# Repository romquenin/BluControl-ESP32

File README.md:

# BluControl-ESP32: Dreamcast & GameCube

Wireless mods for original retro controllers, built on [BluControl-ESP32](https://github.com/JPZV/BluControl-ESP32) by JPZV.

An ESP32 is placed inside the controller and reads it the way the console would. The controller's own board is kept intact. The ESP32 then talks Bluetooth, either as a **Nintendo Switch Pro Controller** or as a generic gamepad for **[BlueRetro](https://github.com/darthcloud/BlueRetro)** adapters.

This fork only keeps what these controllers need. For the other controllers supported by BluControl (N64, SNES, NES, PSX…), use the [original project](https://github.com/JPZV/BluControl-ESP32).

## Controllers

| Controller | Status | Page |
|---|---|---|
| **Sega Dreamcast** | ✅ v1: buttons, stick, analog triggers, and the **VMU** (saves and screen) through a modified BlueRetro, with 4 VMU pages (800 blocks) | [docs/dreamcast.md](docs/dreamcast.md) |
| **Nintendo GameCube** | ✅ v1: in Yakara's style, with rumble through the BluPower GC board · 🚧 v2 "cable mode", with the controller board kept intact | [docs/gamecube.md](docs/gamecube.md) |

Ready-to-flash firmware is in the [Releases](https://github.com/romquenin/BluControl-ESP32/releases). Each release contains the latest firmware for every controller.

## The BluPower GC board

A small board (20.3 × 15.2 mm) made for this project:
- an AP2112K low-dropout 3.3 V regulator for the ESP32, which keeps working as the LiPo battery runs down, where the usual AMS1117 cannot;
- a MOSFET that drives the GameCube rumble motor.

It is fully populated for the GameCube version 1. The Dreamcast and the GameCube cable mode only use its regulator. KiCad project, Gerbers and JLCPCB files are in [`hardware/blupower_gc/`](hardware/blupower_gc). Parts, wiring and ordering: [docs/blupower.md](docs/blupower.md).

## Repository layout

| Path | Content |
|---|---|
| `blu-common/` | Shared components. Dreamcast Maple bus driver: `dc_maple.c` |
| `blu-switch/` | Switch Pro Controller mode |
| `blu-generic/` | BLE gamepad mode for BlueRetro, including the VMU service |
| `blu-ota/` | Wi-Fi update mode |
| `configs/` | Build configuration per controller |
| `patches/` | Small changes to JPZV's submodules, applied by `build.sh` |
| `blueretro/` | Patch for BlueRetro v25.04 (Dreamcast VMU support) |
| `hardware/` | BluPower GC board (KiCad, Gerbers, JLCPCB files) |
| `docs/` | Documentation |

## Building

Requires **ESP-IDF v5.0** and Node.js (for the update web page).

```sh
git clone --recursive https://github.com/romquenin/BluControl-ESP32
cd BluControl-ESP32
. $IDF_PATH/export.sh
./build.sh dreamcast    # or: ./build.sh gamecube
```

The script applies the patches, builds the three modes, and writes two files to `release/`:
- `BluControl_<config>_FULL_0x0.bin`: full USB flash at address 0x0;
- `BluControl_<config>.updpkg`: Wi-Fi update.

The modified BlueRetro is built separately: see [blueretro/README.md](blueretro/README.md).

## Credits

- **[JPZV](https://github.com/JPZV)**, author of [BluControl-ESP32](https://github.com/JPZV/BluControl-ESP32), which this project is built on, and of the forks it uses: [BluControl-SDK-ESP32](https://github.com/JPZV/BluControl-SDK-ESP32), [HOJA-LIB-ESP32](https://github.com/JPZV/HOJA-LIB-ESP32), [ESP32-BLE-Gamepad-idf](https://github.com/JPZV/ESP32-BLE-Gamepad-idf), [esp-nimble-cpp](https://github.com/JPZV/esp-nimble-cpp).
- The original authors of those libraries:
  - **HandHeldLegend**: HOJA-LIB-ESP32, the Switch Pro Controller emulation;
  - **[lemmingDev](https://github.com/lemmingDev)**: ESP32-BLE-Gamepad;
  - **[h2zero](https://github.com/h2zero)**: esp-nimble-cpp.
- **[darthcloud](https://github.com/darthcloud)**: [BlueRetro](https://github.com/darthcloud/BlueRetro). The Dreamcast VMU support is a patch on BlueRetro v25.04.
- **[dpedu.io](https://dpedu.io/article/2015-03-11/nintendo-64-joystick-pinout-arduino)**: credited by the original BluControl for his article on N64 analogs.
- **[Yakara](https://github.com/yakaracolombia)**: for the [GameCube wireless tutorial](https://github.com/yakaracolombia/esp32-online-tool/blob/main/gamecube.md) that inspired our GameCube work.

## License

Same license as BluControl-ESP32: [CC BY-NC-SA 4.0](LICENSE). Non-commercial use only, with attribution, and derivatives must be shared under the same license. Submodules and the BlueRetro patch keep their own licenses: GPL-3.0 for BluControl-SDK, CC BY-NC-SA 4.0 for HOJA-LIB, MIT for ESP32-BLE-Gamepad, Apache-2.0 for esp-nimble-cpp and BlueRetro.

Maintained by [romquenin](https://github.com/romquenin).

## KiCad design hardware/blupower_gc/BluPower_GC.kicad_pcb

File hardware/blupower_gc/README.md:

# BluPower GC: design files

KiCad project, schematic (PDF), JLCPCB fabrication files (`fab/`) and generation scripts (`tools/`).

Documentation, parts list, pinout and wiring: [docs/blupower.md](../../docs/blupower.md).

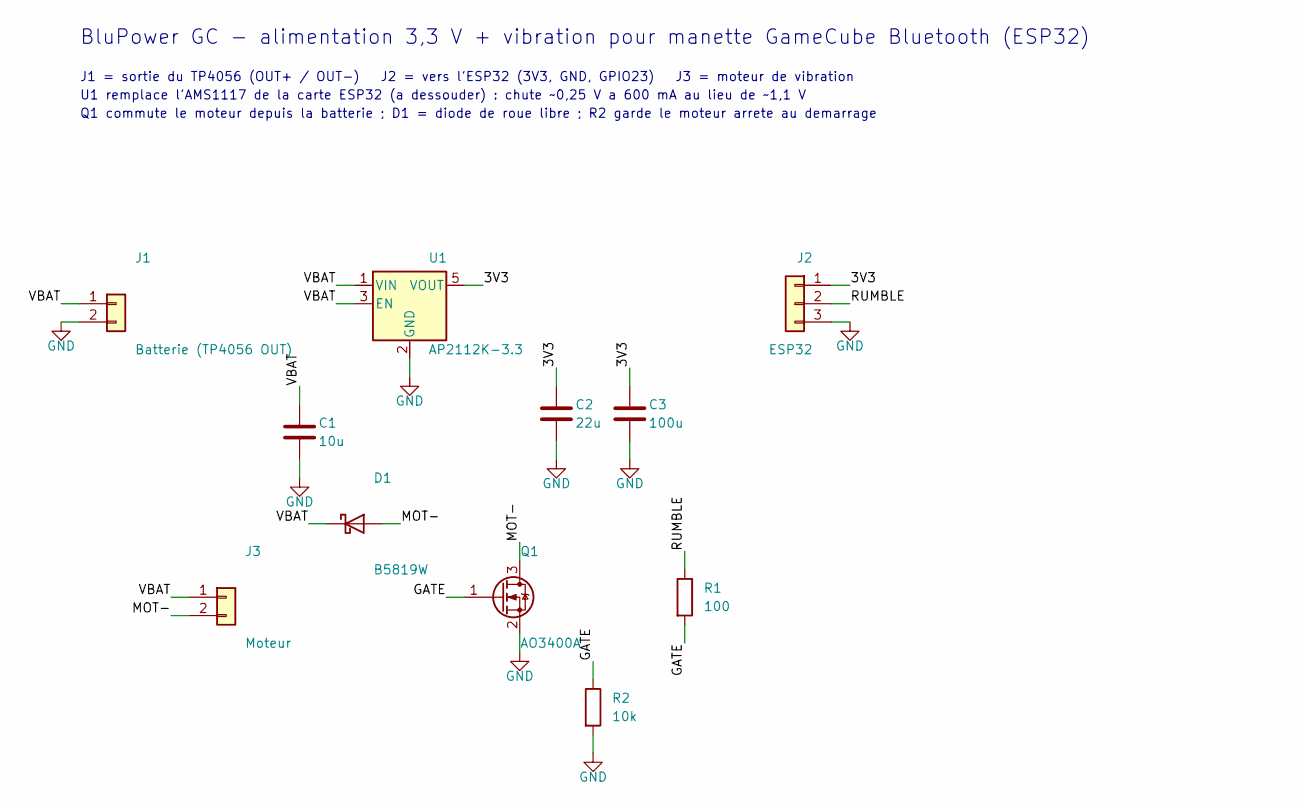
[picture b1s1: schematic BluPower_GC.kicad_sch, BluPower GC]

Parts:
C1: 10u; C_0805_2012Metric; MPN CL21A106KAYNNNE; LCSC C15850
C2: 22u; C_0805_2012Metric; MPN CL21A226MAQNNNE; LCSC C45783
C3: 100u; C_1206_3216Metric; MPN CL31A107MQHNNNE; LCSC C15008
D1: B5819W; D_SOD-123; MPN B5819W; LCSC C8598
J1: Batterie (TP4056 OUT); PinHeader_1x02_P2.54mm_Vertical
J2: ESP32; PinHeader_1x03_P2.54mm_Vertical
J3: Moteur; PinHeader_1x02_P2.54mm_Vertical
Q1: AO3400A; SOT-23; MPN AO3400A; LCSC C20917
R1: 100; R_0805_2012Metric; MPN 0805W8F1000T5E; LCSC C17408
R2: 10k; R_0805_2012Metric; MPN 0805W8F1002T5E; LCSC C17414
U1: AP2112K-3.3; SOT-23-5; MPN AP2112K-3.3TRG1; LCSC C51118

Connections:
/3V3: C2.1, C3.1, J2.1, U1.5 (VOUT)
/GATE: Q1.1 (G), R1.2, R2.1
/MOT-: D1.2 (A), J3.2, Q1.3 (D)
/RUMBLE: J2.2, R1.1
/VBAT: C1.1, D1.1 (K), J1.1, J3.1, U1.1 (VIN), U1.3 (EN)
GND: C1.2, C2.2, C3.2, J1.2, J2.3, Q1.2 (S), R2.2, U1.2 (GND)

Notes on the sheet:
BluPower GC - alimentation 3,3 V + vibration pour manette GameCube Bluetooth (ESP32)
J1 = sortie du TP4056 (OUT+ / OUT-) J2 = vers l'ESP32 (3V3, GND, GPIO23) J3 = moteur de vibration
U1 remplace l'AMS1117 de la carte ESP32 (a dessouder) : chute ~0,25 V a 600 mA au lieu de ~1,1 V
Q1 commute le moteur depuis la batterie ; D1 = diode de roue libre ; R2 garde le moteur arrete au demarrage

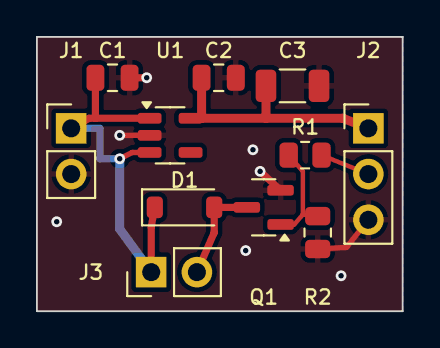
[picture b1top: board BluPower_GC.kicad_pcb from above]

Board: 2 copper layers, 20.3 x 15.2 mm, 11 parts (0 on the bottom side), 6 nets.

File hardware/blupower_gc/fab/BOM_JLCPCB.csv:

Comment,Designator,Footprint,LCSC Part #
10u,C1,C_0805_2012Metric,C15850
22u,C2,C_0805_2012Metric,C45783
100u,C3,C_1206_3216Metric,C15008
B5819W,D1,D_SOD-123,C8598
AO3400A,Q1,SOT-23,C20917
100,R1,R_0805_2012Metric,C17408
10k,R2,R_0805_2012Metric,C17414
AP2112K-3.3,U1,SOT-23-5,C51118
